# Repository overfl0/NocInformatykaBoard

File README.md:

Noc Informatyka Board
=====================

In this repository you'll find all the files related to the identifier given to every attendee of the Noc Informatyka^8 conference. You can find *[details]* here *(Polish)*.

This identifier was also a fully compatible Digispark clone.

Directories
===========

Schematics
----------

This directory holds the *[Eagle]* files used to create and produce the PCB for the identifier. The Eagle version that was used was 6.5.

Firmware
--------

This directory holds the micronucleus bootloader firmware that allows the badge to communicate with a PC and to upload sketches (programs) over the USB connector present on the board.

To upload a new firmware you either need to use an external HVSP programmer or use the virus-like firmware upgrade method.

#### Upload using an external HVSP programmer

Bear in mind that the microcontroller has its reset pin disabled. What this means is that regular ISP programmers (like USBasp) will not be able to program the board unless you reset the fuses with a HVSP programmer or something like *[Attiny fusebit Doctor]*.

```
make
make fuse
make flash
make disablereset
```

#### Upload using the virus-like method

This method has not been tested by us. **Use at your own risk!** See *upgrade* directory for details.

NocInformatyka2014
------------------

This directory holds the sketch preloaded on the badge. If for some reason you would like to revert to the original program, just upload this sketch to the board.

[eagle]:http://www.cadsoftusa.com/eagle-pcb-design-software/product-overview/?language=en
[attiny fusebit doctor]:http://www.instructables.com/id/AVR-Attiny-fusebit-doctor-HVSP/
[details]:http://nocinformatyka.pl/board/

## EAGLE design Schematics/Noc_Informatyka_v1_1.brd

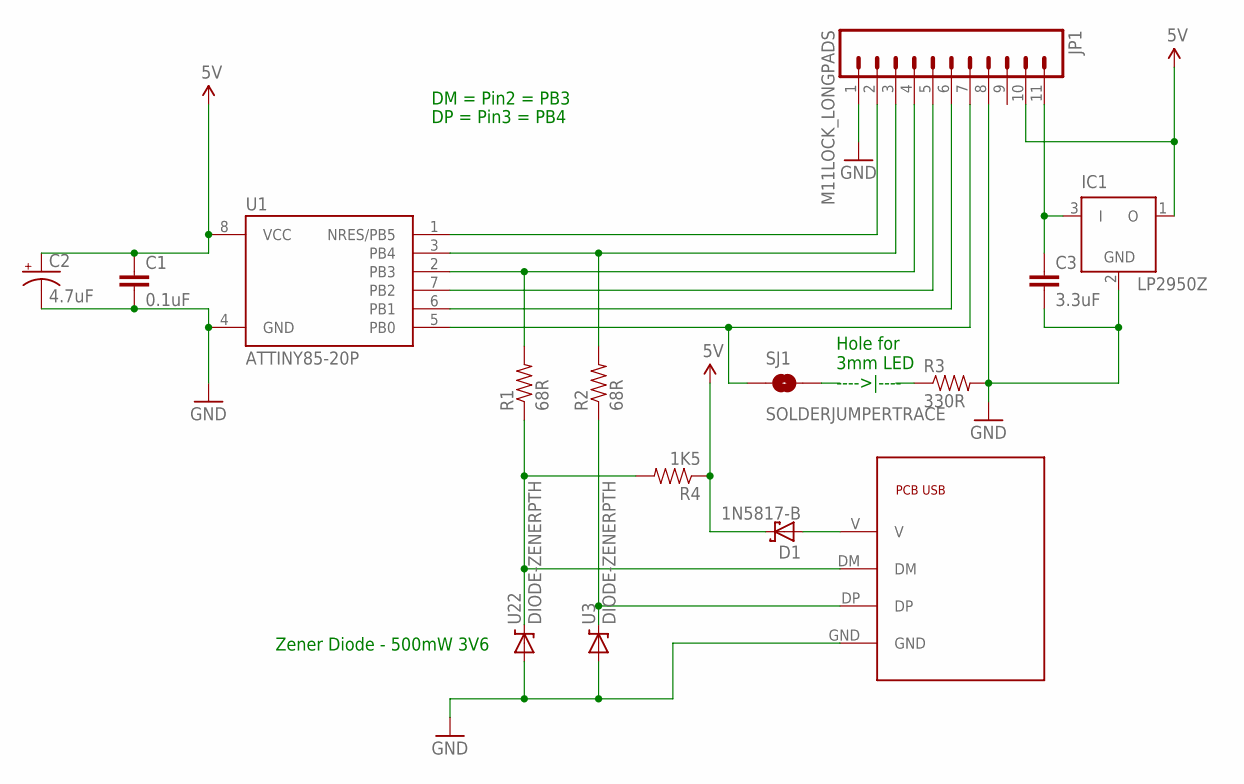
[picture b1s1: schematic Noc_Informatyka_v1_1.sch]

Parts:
C1: 0.1uF; CAP-PTH-SMALLEZ
C2: 4.7uF; CPOL-RADIAL-10UF-25V
C3: 3.3uF; CAP-PTH-5MM
D1: 1N5817-B; DO41-7.6
IC1: LP2950Z; TO92
JP1: M11LOCK_LONGPADS; 1X11_LOCK_LONGPADS
R1, R2: 68R; AXIAL-0.3EZ
R3: 330R; AXIAL-0.3EZ
R4: 1K5; AXIAL-0.3EZ
SJ1: SOLDERJUMPERTRACE; SJ_2S-TRACE
U1: ATTINY85-20P; PDIP08_300MIL
U3, U22: DIODE-ZENERPTH; DIODE-ZENER
U$1: PCB_USBNOBACK; PCB_USB

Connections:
5V: C1.1, C2.1 (+), D1.C, IC1.1 (O), JP1.10, R4.P$1 (1), U1.8 (VCC)
GND: C1.2, C2.2 (-), C3.2, IC1.2 (GND), JP1.1, JP1.8, R3.P$2 (2), U1.4 (GND), U3.P$2 (A), U22.P$2 (A), U$1.GND
unnamed: R1.P$1 (1), R4.P$2 (2), U22.P$1 (C), U$1.DM
unnamed: JP1.2, U1.1 (NRES/PB5)
unnamed: JP1.3, R2.P$2 (2), U1.3 (PB4)
unnamed: JP1.4, R1.P$2 (2), U1.2 (PB3)
unnamed: JP1.5, U1.7 (PB2)
unnamed: JP1.6, U1.6 (PB1)
unnamed: JP1.7, SJ1.1, U1.5 (PB0)
unnamed: C3.1, IC1.3 (I), JP1.11
unnamed: R2.P$1 (1), U3.P$1 (C), U$1.DP
unnamed: D1.A, U$1.V

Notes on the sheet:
DM = Pin2 = PB3
DP = Pin3 = PB4
Hole for 3mm LED ---->|----
Zener Diode - 500mW 3V6

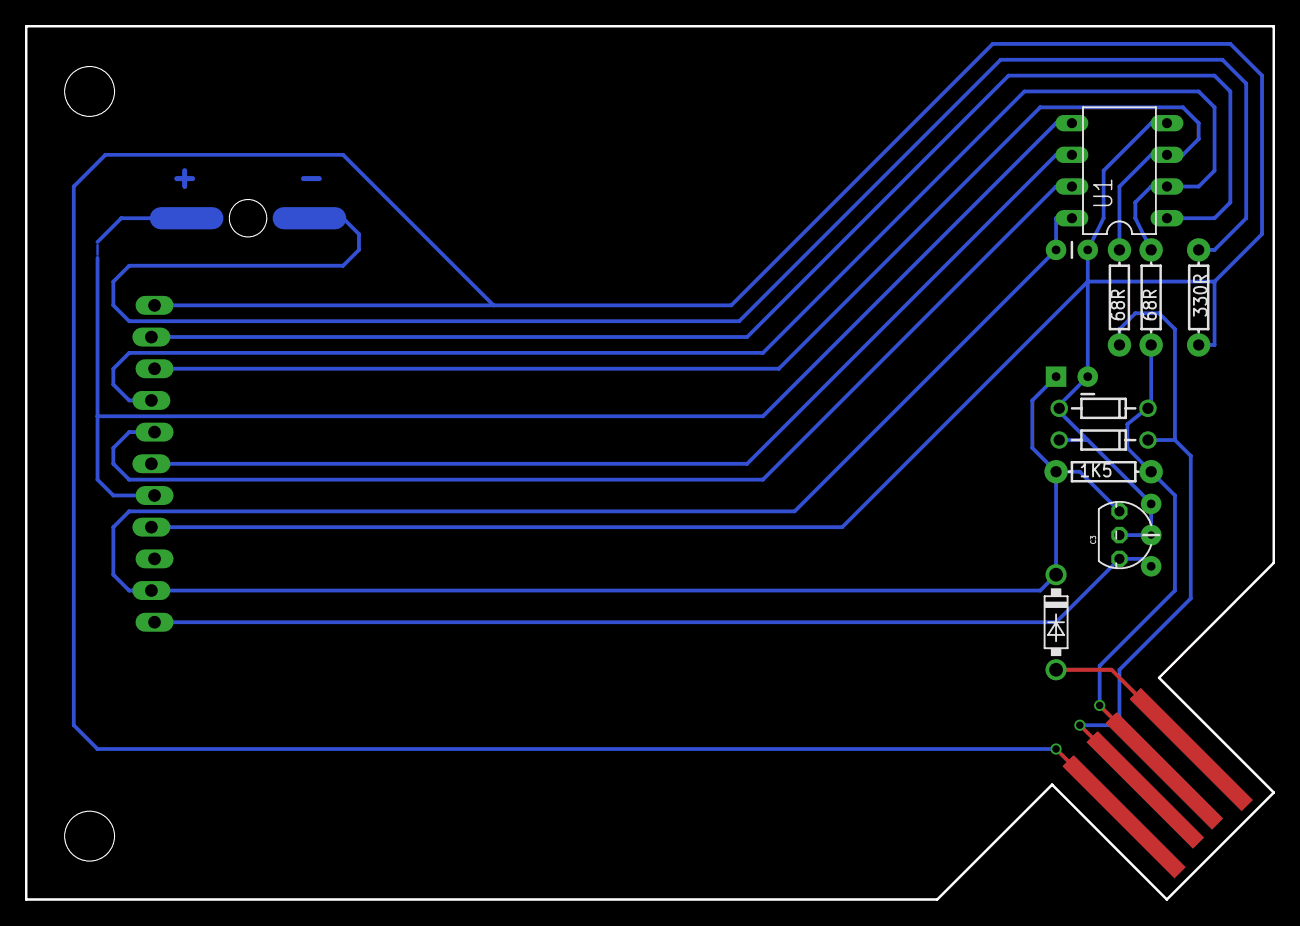
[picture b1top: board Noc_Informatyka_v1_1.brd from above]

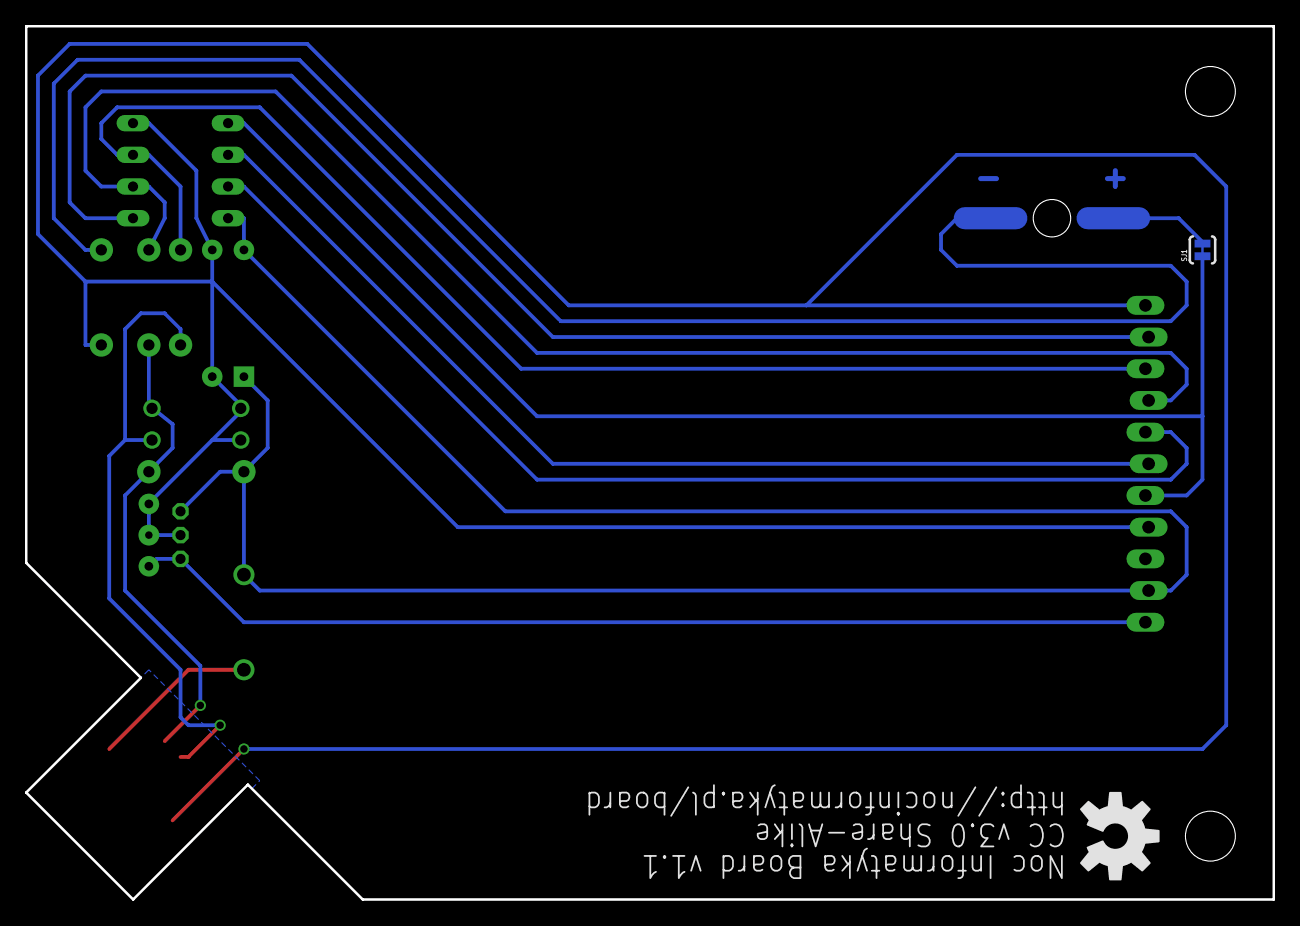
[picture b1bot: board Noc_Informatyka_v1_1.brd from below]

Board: 2 copper layers, 100.0 x 70.0 mm, 16 parts (2 on the bottom side), 12 nets.

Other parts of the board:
U$2: OSHW-LOGO-L

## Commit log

2014-06-07 Changed microcontroller fuses (brownout protection set to 4.5V) Changed bootloader timeout from 5 to 3 seconds
2014-06-07 Small cleanup
2014-06-07 Added the program that was originally uploaded to the board the day of the conference
2014-06-07 Added Noc Informatyka Board schematics
2014-06-08 Added readme.md

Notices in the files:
parts and their libraries:
SparkFun-Capacitors: Licensing: CC v3.0 Share-Alike You are welcome to use this library for commercial purposes.
